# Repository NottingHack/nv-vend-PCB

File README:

PCB for MDB cashless device for Nottingham Hackspace

https://wiki.nottinghack.org.uk/wiki/Vending_Machine

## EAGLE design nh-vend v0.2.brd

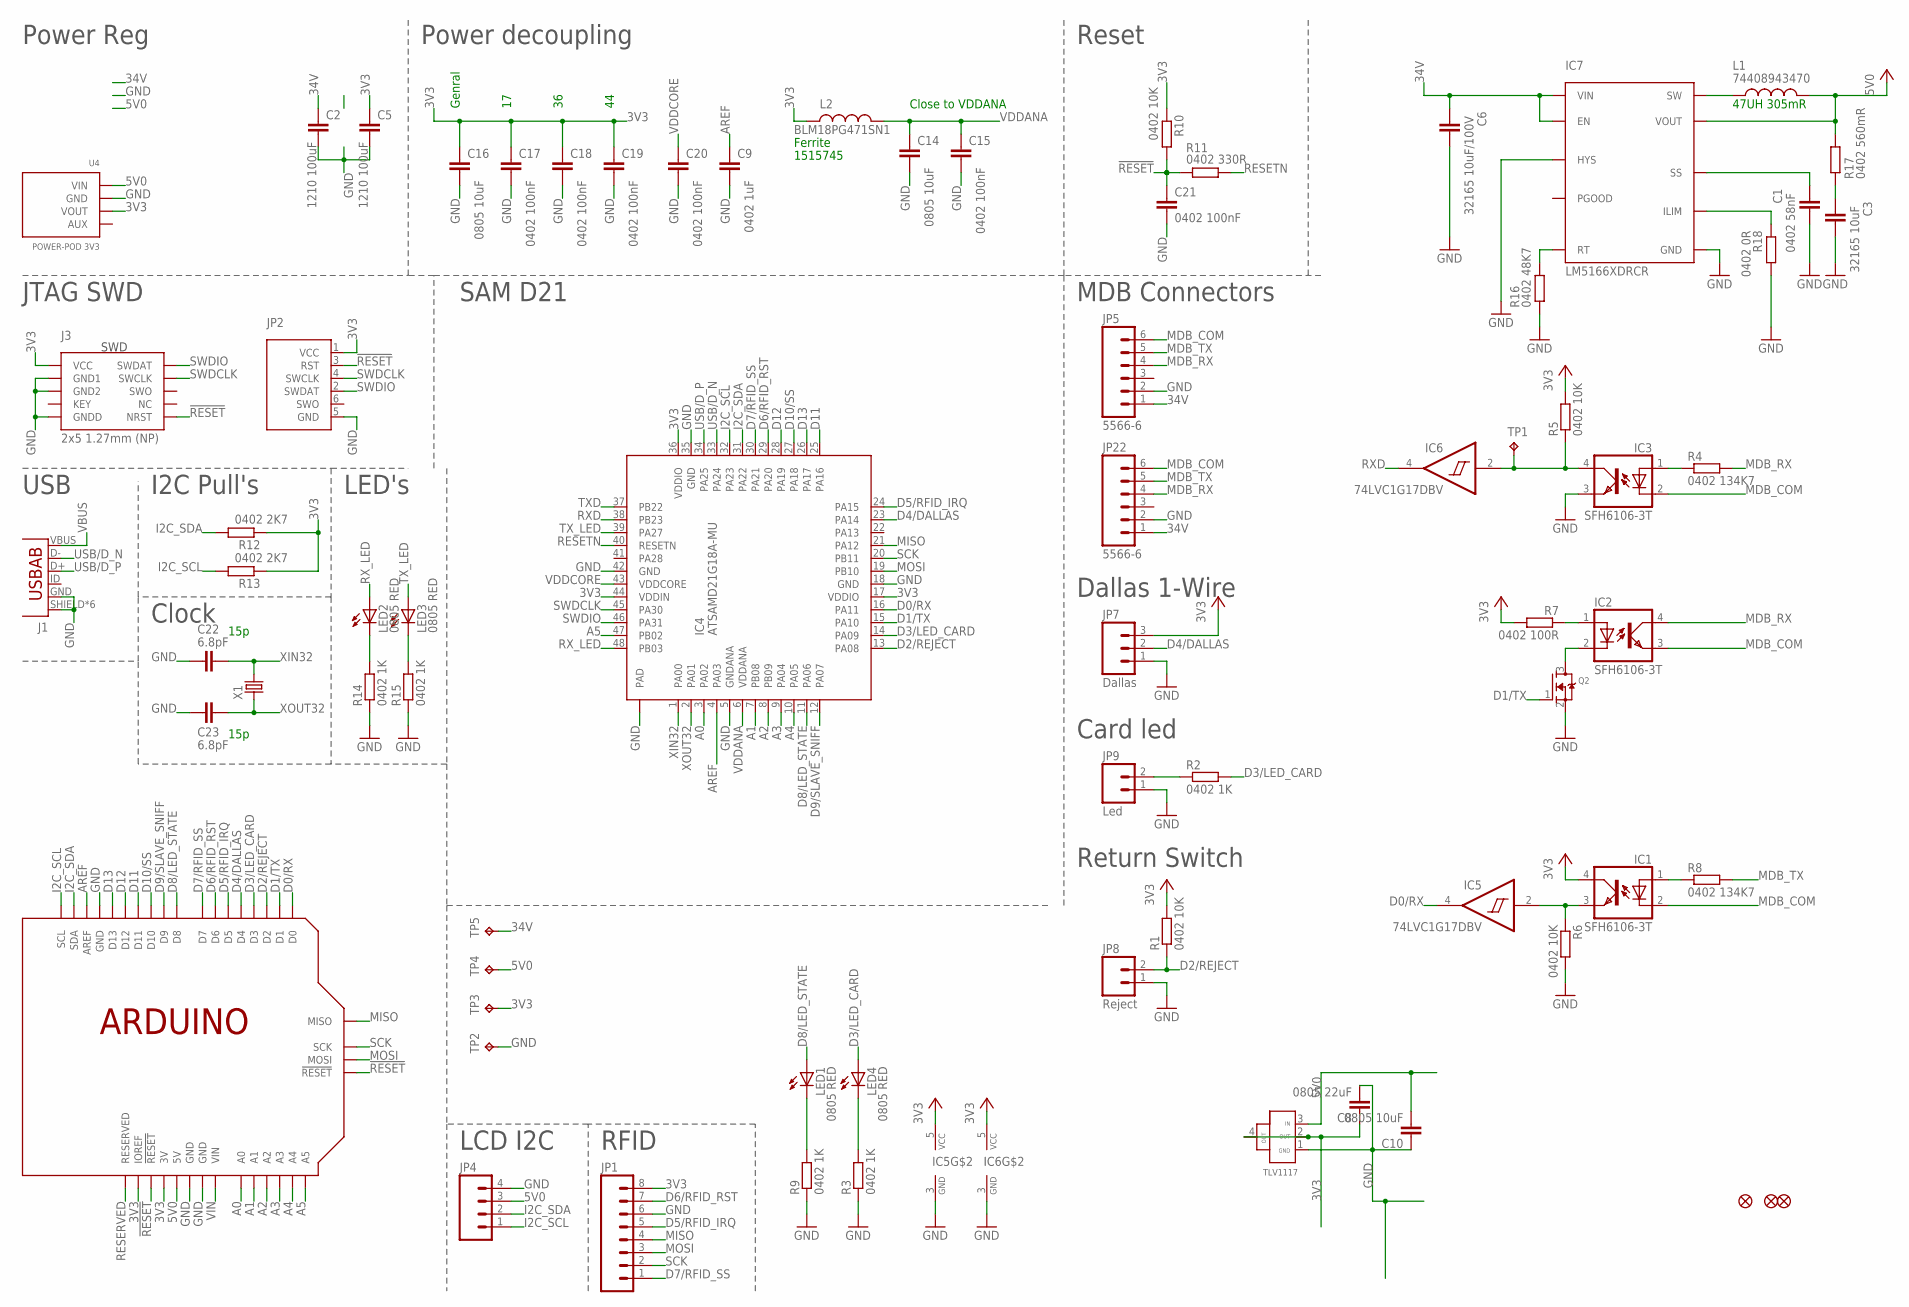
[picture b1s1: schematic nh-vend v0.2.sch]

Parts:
C1: 0402 58nF; C0402-SMALLER
C2, C5: 1210 100uF; C1210
C3: 32165 10uF; C3216
C6: 32165 10uF/100V; C3216
C8: 0805 22uF; C0805
C9: 0402 1uF; C0402-SMALLER
C10: 0805 10uF; C0805
C14, C16: 0805 10uF; C0805K
C15, C17, C18, C19, C20, C21: 0402 100nF; C0402-SMALLER
C22, C23: 6.8pF; C0402-SMALLER
IC1, IC2, IC3: SFH6106-3T; SO04
IC4: ATSAMD21G18A-MU; QFN48-LWK
IC5, IC6: 74LVC1G17DBV; SOT23-5
IC7: LM5166XDRCR; VSON-10
J1: ZX62-AB-5PA(11); USB-AB-MICRO-SMD_LWK; FARNELL 2293755
J3: 2x5 1.27mm (NP); PINHEAD_2X05_127; FARNELL 1865285
JP1: M081X08; 1X08
JP2: (NP); TC2030-MCP-NL
JP3, JP6, JP10: FIDUCIAL1X2.5-STOP; FIDUCIAL-1X2.5-STOP
JP4: M04PTH; 1X04
JP5, JP22: 5566-6; FARNELL 9732101 or 1697112
JP7: Dallas; SCREWTERMINAL-5MM-3
JP8: Reject; SCREWTERMINAL-5MM-2
JP9: Led; SCREWTERMINAL-5MM-2
L1: 74408943470; WE-SPC_48XX
L2: BLM18PG471SN1; C0603K-SMALL
LED1, LED2, LED3, LED4: 0805 RED; LED-0805-1206
Q2: MOSFET-N-SOT23-SPARK; SOT23-3
R1, R5, R6, R10: 0402 10K; R0402-SMALLER
R2, R3, R9, R14, R15: 0402 1K; R0402-SMALLER
R4, R8: 0402 134K7; R0402-SMALLER
R7: 0402 100R; R0402-SMALLER
R11: 0402 330R; R0402-SMALLER
R12, R13: 0402 2K7; R0402-SMALLER
R16: 0402 48K7; R0402-SMALLER
R17: 0402 560mR; R0402-SMALLER
R18: 0402 0R; R0402-SMALLER
TP1, TP2, TP3, TP4, TP5: TPPAD1-10-ROUND; P1-10-ROUND-CAN
U1: ARDUINOSPI-REFRENCE; ARDUINOR3-LWKTXT-REF-SPI
U03: 1117 3V0; SOT223
U4: POWER-POD 3V3; POWER-POD-LANDING
X1: RESONATOR_EPSON_FC_145

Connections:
3V3: C5.1, C8.1, C16.1, C17.1, C18.1, C19.1, IC1.4 (COL), IC4.17 (VDDIO), IC4.36 (VDDIO), IC4.44 (VDDIN), IC5.5 (VCC), IC6.5 (VCC), J3.1 (VCC), JP1.8, JP2.1 (VCC), JP7.3, L2.1, R1.2, R5.2, R7.2, R10.1, R12.1, R13.1, TP3.TP, U1.3V, U1.IOREF, U03.2 (OUT1), U03.4 (OUT2), U4.3 (VOUT)
5V0: C10.2, IC7.8 (VOUT), JP4.3, L1.2, R17.1, TP4.TP, U1.5V, U1.5V@ISP (5V), U03.3 (IN), U4.1 (VIN)
34V: C2.1, C6.1, IC7.2 (VIN), IC7.7 (EN), JP5.1, JP22.1, TP5.TP
!RESET: C21.1, J3.10 (NRST), JP2.3 (RST), R10.2, R11.1, U1.!RESET, U1.!RESET@ISP (!RESET)
A0: IC4.3 (PA02), U1.A0
A1: IC4.7 (PB08), U1.A1
A2: IC4.8 (PB09), U1.A2
A3: IC4.9 (PA04), U1.A3
A4: IC4.10 (PA05), U1.A4
A5: IC4.47 (PB02), U1.A5
AREF: C9.1, IC4.4 (PA03), U1.AREF
D0/RX: IC4.16 (PA11), IC5.4 (O), U1.D0
D1/TX: IC4.15 (PA10), Q2.1 (G), U1.D1
D2/REJECT: IC4.13 (PA08), JP8.2, R1.1, U1.D2
D3/LED_CARD: IC4.14 (PA09), LED4.A, R2.2, U1.D3
D4/DALLAS: IC4.23 (PA14), JP7.2, U1.D4
D5/RFID_IRQ: IC4.24 (PA15), JP1.5, U1.D5
D6/RFID_RST: IC4.29 (PA20), JP1.7, U1.D6
D7/RFID_SS: IC4.30 (PA21), JP1.1, U1.D7
D8/LED_STATE: IC4.11 (PA06), LED1.A, U1.D8
D9/SLAVE_SNIFF: IC4.12 (PA07), U1.D9
D10/SS: IC4.27 (PA18), U1.D10
D11: IC4.25 (PA16), U1.D11
D12: IC4.28 (PA19), U1.D12
D13: IC4.26 (PA17), U1.D13
GND: C1.2, C2.2, C3.2, C5.2, C6.2, C8.2, C9.2, C10.1, C14.2, C15.2, C16.2, C17.2, C18.2, C19.2, C20.2, C21.2, C22.2, C23.2, IC3.3 (EMIT), IC4.5 (GNDANA), IC4.18 (GND), IC4.35 (GND), IC4.42 (GND), IC4.EXP (PAD), IC5.3 (GND), IC6.3 (GND), IC7.9 (HYS), IC7.10 (GND), IC7.PAD (GND), J1.GND, J1.SHIELD, J1.SHIELD@0 (SHIELD), J1.SHIELD@1 (SHIELD), J1.SHIELD@2 (SHIELD), J1.SHIELD@3 (SHIELD), J1.SHIELD@5 (SHIELD), J3.3 (GND1), J3.5 (GND2), J3.9 (GNDD), JP1.6, JP2.5 (GND), JP4.4, JP5.2, JP7.1, JP8.1, JP9.1, JP22.2, Q2.2 (S), R3.1, R6.2, R9.1, R14.1, R15.1, R16.1, R18.1, TP2.TP, U1.GND@1 (GND), U1.GND@2 (GND), U1.GND@3 (GND), U1.GND@ISP (GND), U03.1 (GND), U4.2 (GND)
I2C_SCL: IC4.32 (PA23), JP4.1, R13.2, U1.SCL
I2C_SDA: IC4.31 (PA22), JP4.2, R12.2, U1.SDA
ILIM: IC7.3 (ILIM), R18.2
LED_R: JP9.2, R2.1
MDB_COM: IC1.2 (C), IC2.3 (EMIT), IC3.2 (C), JP5.6, JP22.6
MDB_RX: IC2.4 (COL), JP5.4, JP22.4, R4.2
MDB_TX: JP5.5, JP22.5, R8.2
MISO: IC4.21 (PA12), JP1.4, U1.MISO
MOSI: IC4.19 (PB10), JP1.3, U1.MOSI
unnamed: IC3.1 (A), R4.1
unnamed: IC1.1 (A), R8.1
unnamed: LED4.C, R3.2
unnamed: IC2.1 (A), R7.1
unnamed: IC2.2 (C), Q2.3 (D)
unnamed: LED1.C, R9.2
unnamed: LED2.C, R14.2
unnamed: LED3.C, R15.2
unnamed: IC7.5 (RT), R16.2
unnamed: C3.1, R17.2
RESERVED: U1.RESERVED
RESETN: IC4.40 (RESETN), R11.2
RX: IC1.3 (EMIT), IC5.2 (I), R6.1
RXD: IC4.38 (PB23), IC6.4 (O)
RX_LED: IC4.48 (PB03), LED2.A
SCK: IC4.20 (PB11), JP1.2, U1.SCK
SLAVE_SNIFF: IC3.4 (COL), IC6.2 (I), R5.1, TP1.TP
SS: C1.1, IC7.4 (SS)
SW: IC7.1 (SW), L1.1
SWDCLK: IC4.45 (PA30), J3.4 (SWCLK), JP2.4 (SWCLK)
SWDIO: IC4.46 (PA31), J3.2 (SWDAT), JP2.2 (SWDAT)
TXD: IC4.37 (PB22)
TX_LED: IC4.39 (PA27), LED3.A
USB/D_N: IC4.33 (PA24), J1.D-
USB/D_P: IC4.34 (PA25), J1.D+
VBUS: J1.VBUS
VDDANA: C14.1, C15.1, IC4.6 (VDDANA), L2.2
VDDCORE: C20.1, IC4.43 (VDDCORE)
VIN: U1.VIN
XIN32: C22.1, IC4.1 (PA00), X1.P$2 (2)
XOUT32: C23.1, IC4.2 (PA01), X1.P$1 (1)

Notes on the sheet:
Close to VDDANA
Ferrite
Genral
1515745
15p
JTAG SWD
LCD I2C
RFID
Power Reg
USB
I2C Pull's
Clock
Power decoupling
LED's
Reset
SAM D21
MDB Connectors
Dallas 1-Wire
Card led
Return Switch
47UH 305mR

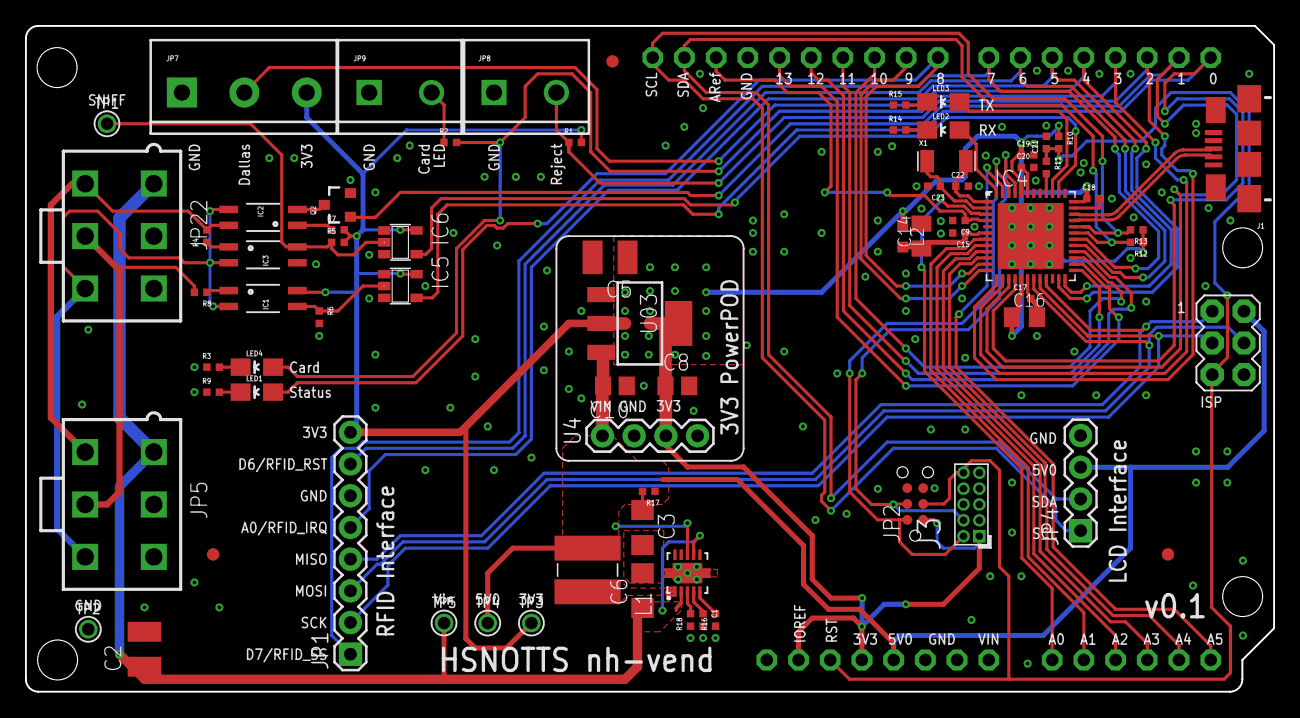
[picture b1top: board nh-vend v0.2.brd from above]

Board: 2 copper layers, 100.0 x 53.3 mm, 72 parts (0 on the bottom side), 62 nets.

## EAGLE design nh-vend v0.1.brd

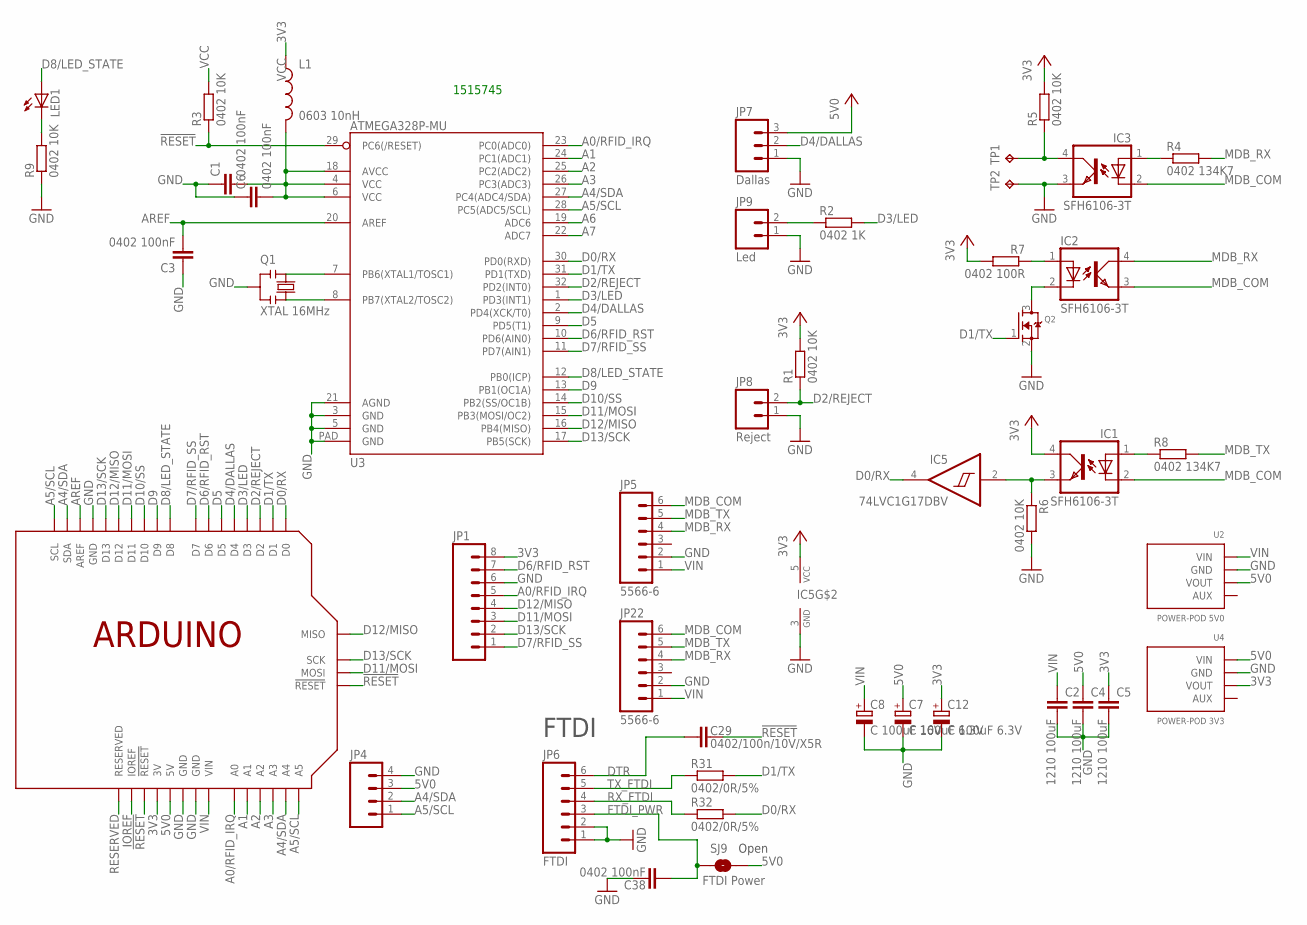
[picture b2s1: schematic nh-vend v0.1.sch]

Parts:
C1, C3, C6, C38: 0402 100nF; C0402-SMALLER
C2, C4, C5: 1210 100uF; C1210
C7, C12: C 100uF 6.3V; PANASONIC_C
C8: C 100uF 16V; PANASONIC_C
C29: 0402/100n/10V/X5R; C0402-ARDUINO-ROUND
IC1, IC2, IC3: SFH6106-3T; SO04
IC5: 74LVC1G17DBV; SOT23-5
JP1: M081X08; 1X08
JP4: M04PTH; 1X04
JP5, JP22: 5566-6; FARNELL 9732101 or 1697112
JP6: FTDI; 1X06
JP7: Dallas; SCREWTERMINAL-5MM-3
JP8: Reject; SCREWTERMINAL-5MM-2
JP9: Led; SCREWTERMINAL-5MM-2
L1: 0603 10nH; C0603K-SMALL
LED1: LED0805-1206; LED-0805-1206
Q1: XTAL 16MHz; RESONATOR
Q2: MOSFET-N-SOT23-SPARK; SOT23-3
R1, R3, R5, R6, R9: 0402 10K; R0402-SMALLER
R2: 0402 1K; R0402-SMALLER
R4, R8: 0402 134K7; R0402-SMALLER
R7: 0402 100R; R0402-SMALLER
R31, R32: 0402/0R/5%; R0402-ARDUINO-ROUND
SJ9: FTDI Power; SJ_2S-NO
TP1, TP2: TPPAD1-10-ROUND; P1-10-ROUND-CAN
U1: ARDUINOSPI-REFRENCE; ARDUINOR3-LWKTXT-REF-SPI
U2: POWER-POD 5V0; POWER-POD-LANDING
U3: ATMEGA328P-MU; MLF32-SHORT-CREAM
U4: POWER-POD 3V3; POWER-POD-LANDING

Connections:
3V3: C5.1, C12.+, IC1.4 (COL), IC5.5 (VCC), JP1.8, L1.1, R1.2, R5.2, R7.2, U1.3V, U4.3 (VOUT)
5V0: C4.1, C7.+, JP4.3, JP7.3, SJ9.2, U1.5V, U1.5V@ISP (5V), U2.3 (VOUT), U4.1 (VIN)
!RESET: C29.1, R3.1, U1.!RESET, U1.!RESET@ISP (!RESET), U3.29 (PC6(/RESET))
A0/RFID_IRQ: JP1.5, U1.A0, U3.23 (PC0(ADC0))
A1: U1.A1, U3.24 (PC1(ADC1))
A2: U1.A2, U3.25 (PC2(ADC2))
A3: U1.A3, U3.26 (PC3(ADC3))
A4/SDA: JP4.2, U1.A4, U1.SDA, U3.27 (PC4(ADC4/SDA))
A5/SCL: JP4.1, U1.A5, U1.SCL, U3.28 (PC5(ADC5/SCL))
A6: U3.19 (ADC6)
A7: U3.22 (ADC7)
AREF: C3.2, U1.AREF, U3.20 (AREF)
D0/RX: IC5.4 (O), R32.2, U1.D0, U3.30 (PD0(RXD))
D1/TX: Q2.1 (G), R31.2, U1.D1, U3.31 (PD1(TXD))
D2/REJECT: JP8.2, R1.1, U1.D2, U3.32 (PD2(INT0))
D3/LED: R2.2, U1.D3, U3.1 (PD3(INT1))
D4/DALLAS: JP7.2, U1.D4, U3.2 (PD4(XCK/T0))
D5: U1.D5, U3.9 (PD5(T1))
D6/RFID_RST: JP1.7, U1.D6, U3.10 (PD6(AIN0))
D7/RFID_SS: JP1.1, U1.D7, U3.11 (PD7(AIN1))
D8/LED_STATE: LED1.A, U1.D8, U3.12 (PB0(ICP))
D9: U1.D9, U3.13 (PB1(OC1A))
D10/SS: U1.D10, U3.14 (PB2(SS/OC1B))
D11/MOSI: JP1.3, U1.D11, U1.MOSI, U3.15 (PB3(MOSI/OC2))
D12/MISO: JP1.4, U1.D12, U1.MISO, U3.16 (PB4(MISO))
D13/SCK: JP1.2, U1.D13, U1.SCK, U3.17 (PB5(SCK))
DTR: C29.2, JP6.6
FTDI_PWR: C38.2, JP6.3, SJ9.1
GND: C1.1, C2.2, C3.1, C4.2, C5.2, C6.1, C7.-, C8.-, C12.-, C38.1, IC3.3 (EMIT), IC5.3 (GND), JP1.6, JP4.4, JP5.2, JP6.1, JP6.2, JP7.1, JP8.1, JP9.1, JP22.2, Q1.2, Q2.2 (S), R6.2, R9.1, TP2.TP, U1.GND@1 (GND), U1.GND@2 (GND), U1.GND@3 (GND), U1.GND@ISP (GND), U2.2 (GND), U3.3 (GND), U3.5 (GND), U3.21 (AGND), U3.PAD (GND), U4.2 (GND)
IOREF: U1.IOREF
LED_R: JP9.2, R2.1
MDB_COM: IC1.2 (C), IC2.3 (EMIT), IC3.2 (C), JP5.6, JP22.6
MDB_RX: IC2.4 (COL), JP5.4, JP22.4, R4.2
MDB_TX: JP5.5, JP22.5, R8.2
unnamed: IC3.1 (A), R4.1
unnamed: IC1.1 (A), R8.1
unnamed: Q1.1, U3.7 (PB6(XTAL1/TOSC1))
unnamed: Q1.3, U3.8 (PB7(XTAL2/TOSC2))
unnamed: IC3.4 (COL), R5.1, TP1.TP
unnamed: IC2.1 (A), R7.1
unnamed: IC2.2 (C), Q2.3 (D)
unnamed: LED1.C, R9.2
RESERVED: U1.RESERVED
RX: IC1.3 (EMIT), IC5.2 (I), R6.1
RX_FTDI: JP6.4, R32.1
TX_FTDI: JP6.5, R31.1
VCC: C1.2, C6.2, L1.2, R3.2, U3.4 (VCC), U3.6 (VCC), U3.18 (AVCC)
VIN: C2.1, C8.+, JP5.1, JP22.1, U1.VIN, U2.1 (VIN)

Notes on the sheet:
FTDI
Open
1515745

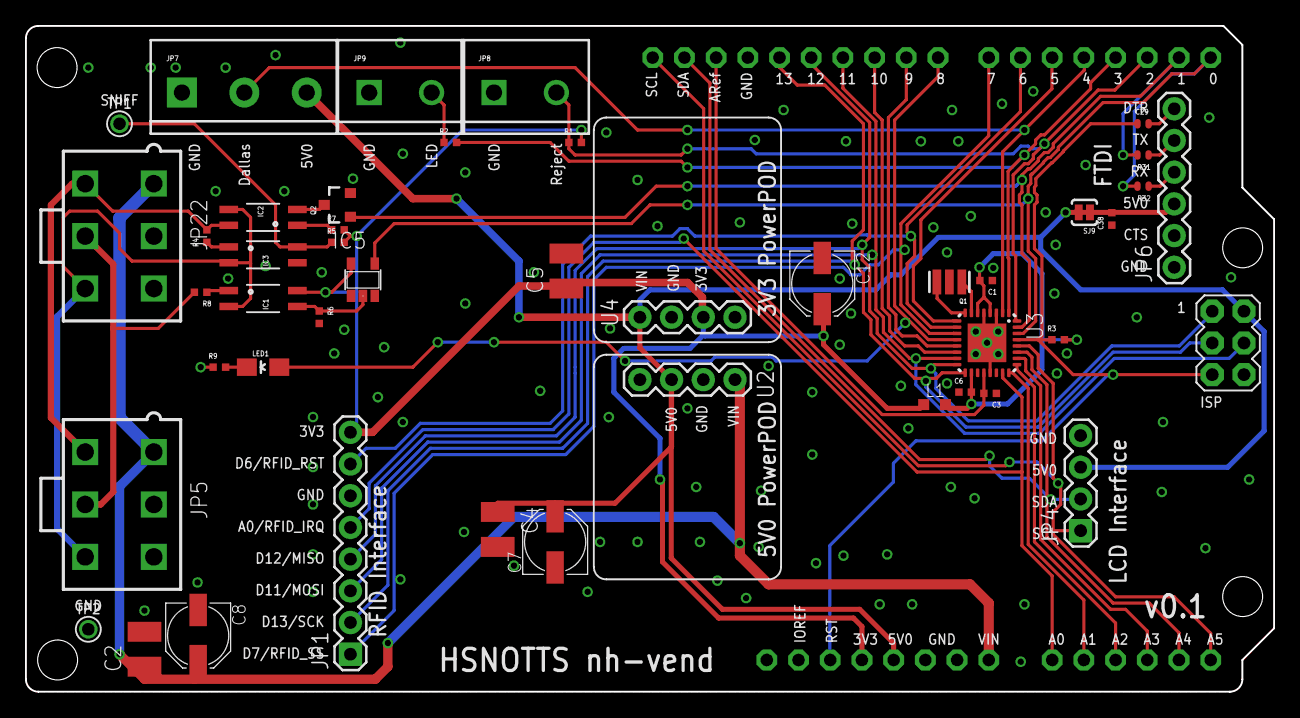
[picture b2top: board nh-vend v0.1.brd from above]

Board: 2 copper layers, 100.0 x 53.3 mm, 45 parts (0 on the bottom side), 44 nets.

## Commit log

2018-07-11 New nh-vend pcb designs
2018-07-16 Add board render

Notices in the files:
parts and their libraries:
SparkFunJan12: Licensing: CC v3.0 Share-Alike You are welcome to use this library for commercial purposes.
TiLDA Mk3 Parts: ©2009 ROFA.cz - modified and updated by Robert Darlington ‹rdarlington@gmail.com›
